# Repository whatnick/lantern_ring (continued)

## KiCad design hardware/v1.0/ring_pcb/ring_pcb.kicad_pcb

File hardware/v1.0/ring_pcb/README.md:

# Single LED choices

White - IN-S126ASUW
InfraRed - 
Red - APHCM2012QBC/D-F01
Orange - APTL3216SECK-01
Yellow - APTL3216SYCK
Green - APTD3216MGC
Blue - SM1206UV-400-IL
Indigo - 
Violet - APTR3216-VFX
UV -

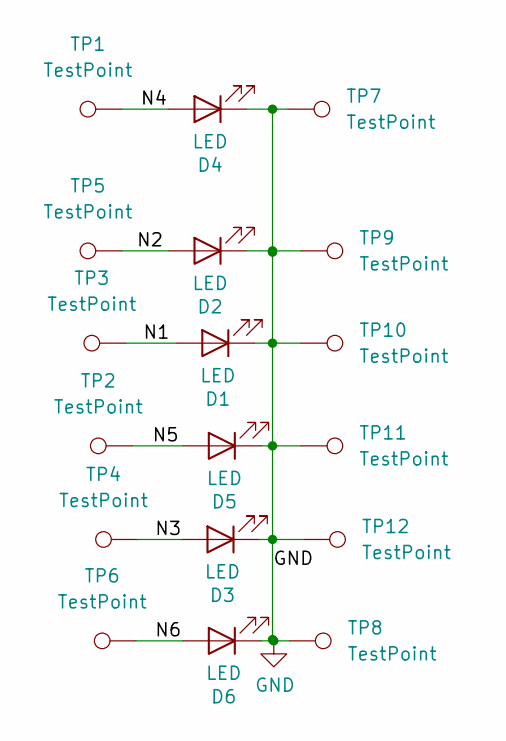
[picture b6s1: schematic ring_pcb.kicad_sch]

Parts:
D1, D2, D3, D4, D5, D6: LED; LED_1206_3216Metric
TP1, TP2, TP3, TP4, TP5, TP6, TP7, TP8, TP9, TP10, TP11, TP12: TestPoint; TestPoint_Pad_1.5x1.5mm

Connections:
/N1: D1.2 (A), TP3.1
/N2: D2.2 (A), TP5.1
/N3: D3.2 (A), TP4.1
/N4: D4.2 (A), TP1.1
/N5: D5.2 (A), TP2.1
/N6: D6.2 (A), TP6.1
GND: D1.1 (K), D2.1 (K), D3.1 (K), D4.1 (K), D5.1 (K), D6.1 (K), TP7.1, TP8.1, TP9.1, TP10.1, TP11.1, TP12.1

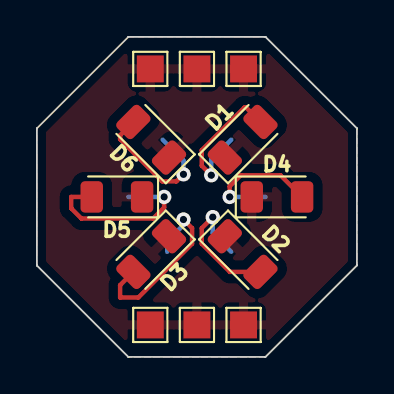
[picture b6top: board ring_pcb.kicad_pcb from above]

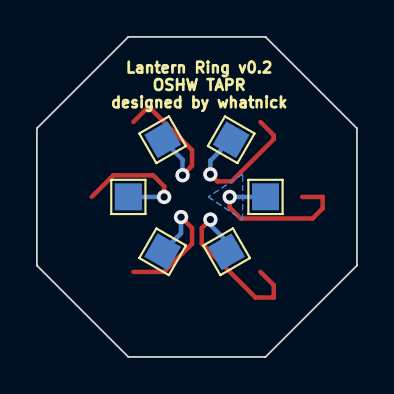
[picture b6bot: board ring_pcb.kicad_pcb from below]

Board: 2 copper layers, 17.8 x 17.8 mm, 18 parts (6 on the bottom side), 7 nets.

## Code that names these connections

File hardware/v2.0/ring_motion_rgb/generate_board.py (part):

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            zone.SetNet(vcc)

    for name in (
        "PB0", "PB1", "PB2", "PB3", "PB4", "PB5",
        "ACC_SCL", "ACC_SDA", "ACC_INT",
        "PWM_R", "PWM_G", "PWM_B",
        "LIMIT_R", "LIMIT_G", "LIMIT_B",
    ):
        add_net(board, nets, name)

    # QFN pad numbers follow the KiCad ATtiny84A-M symbol. The clip's PB0,
    # PB1, and PB2 pads are the native USI programming pins. PB5 is the clip
    # alias for the chip's native PB3/RESET pad; PB3/PB4 are spare probe aliases.
    mcu_pads = {
        "1": "ACC_INT",   # PA4
        "2": "PWM_B",     # PA3
        "3": "ACC_SCL",   # PA2
        "4": "PWM_G",     # PA1
        "5": "PWM_R",     # AREF / PA0
        "8": "GND",
        "9": "VCC",
        "11": "PB0",      # USI DI / MOSI
        "12": "PB1",      # USI DO / MISO
        "13": "PB5",      # PB3 / RESET, clip alias
        "14": "PB2",      # USI USCK / SCK
        "15": "ACC_SDA",  # PA7
        "16": "PB4",      # PA6, spare clip probe alias
        "20": "PB3",      # PA5, spare clip probe alias
        "21": "GND",      # exposed pad
    }
    add_part(
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    add_part(
        board, nets, "Resistor_SMD", "R_0402_1005Metric",
        "R4", "10k RESET pull-up", (5.9, 4.2),
        angle=0, pad_nets={"1": "PB5", "2": "VCC"},
    )
    add_part(
        board, nets, "Capacitor_SMD", "C_0402_1005Metric",
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    # Preserve the exact seven-pad programming-clip grid and front ground
    # anvil datum from the IR board, translated to the mono board center.
    clip = {
        "P1": ((3.0754, 4.6736), "PB0"),
        "P2": ((3.0754, 7.7236), "PB1"),
        "P3": ((0.0254, 4.6736), "PB2"),
        "P4": ((0.0254, 7.7236), "PB3"),
        "P5": ((-3.0246, 4.6736), "PB4"),
        "P6": ((-3.0246, 7.7236), "PB5"),
        "P9": ((0.127, 0.127), "VCC"),
    }
    for reference, (xy, name) in clip.items():
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
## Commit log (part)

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2021-11-14 Initial import
2021-11-14 Add readme
2021-11-17 Add test pads
2021-11-18 First v0.1 cut
2021-11-18 Add gerbers
2021-11-24 Start on MCAD
2021-11-24 Ignore freecad backup files
2021-11-24 Add Cabuchon
2021-12-31 Progress on CAD
2021-12-31 Update pcb to v0.2 for new mounting plan
2021-12-31 More vias and keepouts
2021-12-31 Add structrual spheres
2022-01-01 New PCB and Gerbers
2022-01-01 Add STL export
2022-01-07 Ignore IDE files
2022-01-21 Add fear logo
2022-01-22 Add fear logo supports
2022-01-25 Add will logo
2022-01-30 implement mass computation
2022-01-31 Volume and weight calculation code
2022-02-03 Add more elements to resurrection
2022-02-05 Export death/rebirth stl
2022-02-05 Add rebirth bridge
2022-02-10 Add tindie listing notes
2022-02-12 Rage logo
2022-02-12 Add commercial link
2022-02-14 Add star sapphire logo
2022-02-15 Add hope logo
2022-02-15 Refactor hope logo
2022-02-19 Add empathy logo
2022-02-19 Rename empathy logo for consistency
2022-02-19 Add avarice logo
2022-03-12 Started on custom logo top
2022-03-12 Badly extruded version of logo pending education on shrink wrapping
2022-03-12 Blender solidified
2022-03-12 Bar 38 logo completed
2022-03-14 Start on MTG mana logos
2022-03-19 Added red logo sketch
2022-03-19 Add shapeways links
2022-03-19 Add links to shapeways products
2022-03-19 Sketch white/sun logo for MTG
2022-03-20 Finish green trace
2022-03-20 Complete all MTG traces, add blue logo STL
2022-03-30 Start on Fengshui cover
2022-04-16 Add FengShui Compass
2022-04-23 Add collar for slotting rage logo
2022-04-30 Add collars to all logos
2022-05-10 Add open ring
2022-05-10 Open ring STL
2022-05-29 Add new sizes
2022-06-01 Add size 165
2022-06-01 Add size 165 stl
2022-08-05 Make skull cufflink
2022-08-12 More work on compass
2022-08-27 Add STL for will logo with press fit balls
2022-08-27 EPS for stamps print
2022-09-03 Create 185 size body
2022-09-10 Add remeshed size 185
2022-09-29 Add more cufflinks
2022-10-01 Add red and black STL's
2022-10-09 Add LED part numbers
2022-10-30 #7 Notes on Qi charger design
2022-10-31 #4 Notes for IR details
2022-10-31 #4 Add Links to prior art
2022-11-01 #4 Add SMD version
2022-11-05 Add some pics
2022-11-05 Add pics to README
2022-11-13 Start on InfraRed ring design
2022-11-19 Start wiring up LED driver
2023-02-15 Refresh PCB
2023-02-15 Aisler order
2023-02-15 Add links to products
2023-02-18 Add Images
2023-02-18 Change photo for Purple ring
2023-02-19 Add link to black / white tops
2023-02-24 Reposition parts
2023-02-25 Add IR components
2023-03-18 Add more wiring for LED and power pads
2023-04-30 Start on firmware and ring mods
2023-08-06 Add simple monocolour PCB
2023-08-12 Route PCB
2023-08-12 Fix routing, squash unrouted
2023-08-18 Start implementing controlled APA102
2023-09-10 Make mono PCB smaller
2023-09-10 Add pad at the bottom
2023-11-23 Send PCB to be made
2023-11-24 Add collector connection for PNP
2023-11-26 Routed with smaller PCB
2023-11-28 Choose LED's
2023-11-30 Change transistors and rewire
2023-12-01 Select more parts
2023-12-02 New Gerbers with smaller dual-NPN
2024-01-21 Started on pokemon cufflinks
2024-01-23 Add new 3D energy
2024-01-23 Pascal is messing around
2024-01-23 Pascal is messing around more
2024-01-25 daddy is messing around
2024-03-31 Create BOM
